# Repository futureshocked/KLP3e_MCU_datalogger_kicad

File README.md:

View this project on [CADLAB.io](https://cadlab.io/project/24569). 

# MCU datalogger, a Kicad project

This is the repository for the "MCU datalogger" project.

This is one of the projects from the course [KiCad Like a Pro, 3rd edition](https://techexplorations.com/so/kicad-like-a-pro-3rd-edition/).

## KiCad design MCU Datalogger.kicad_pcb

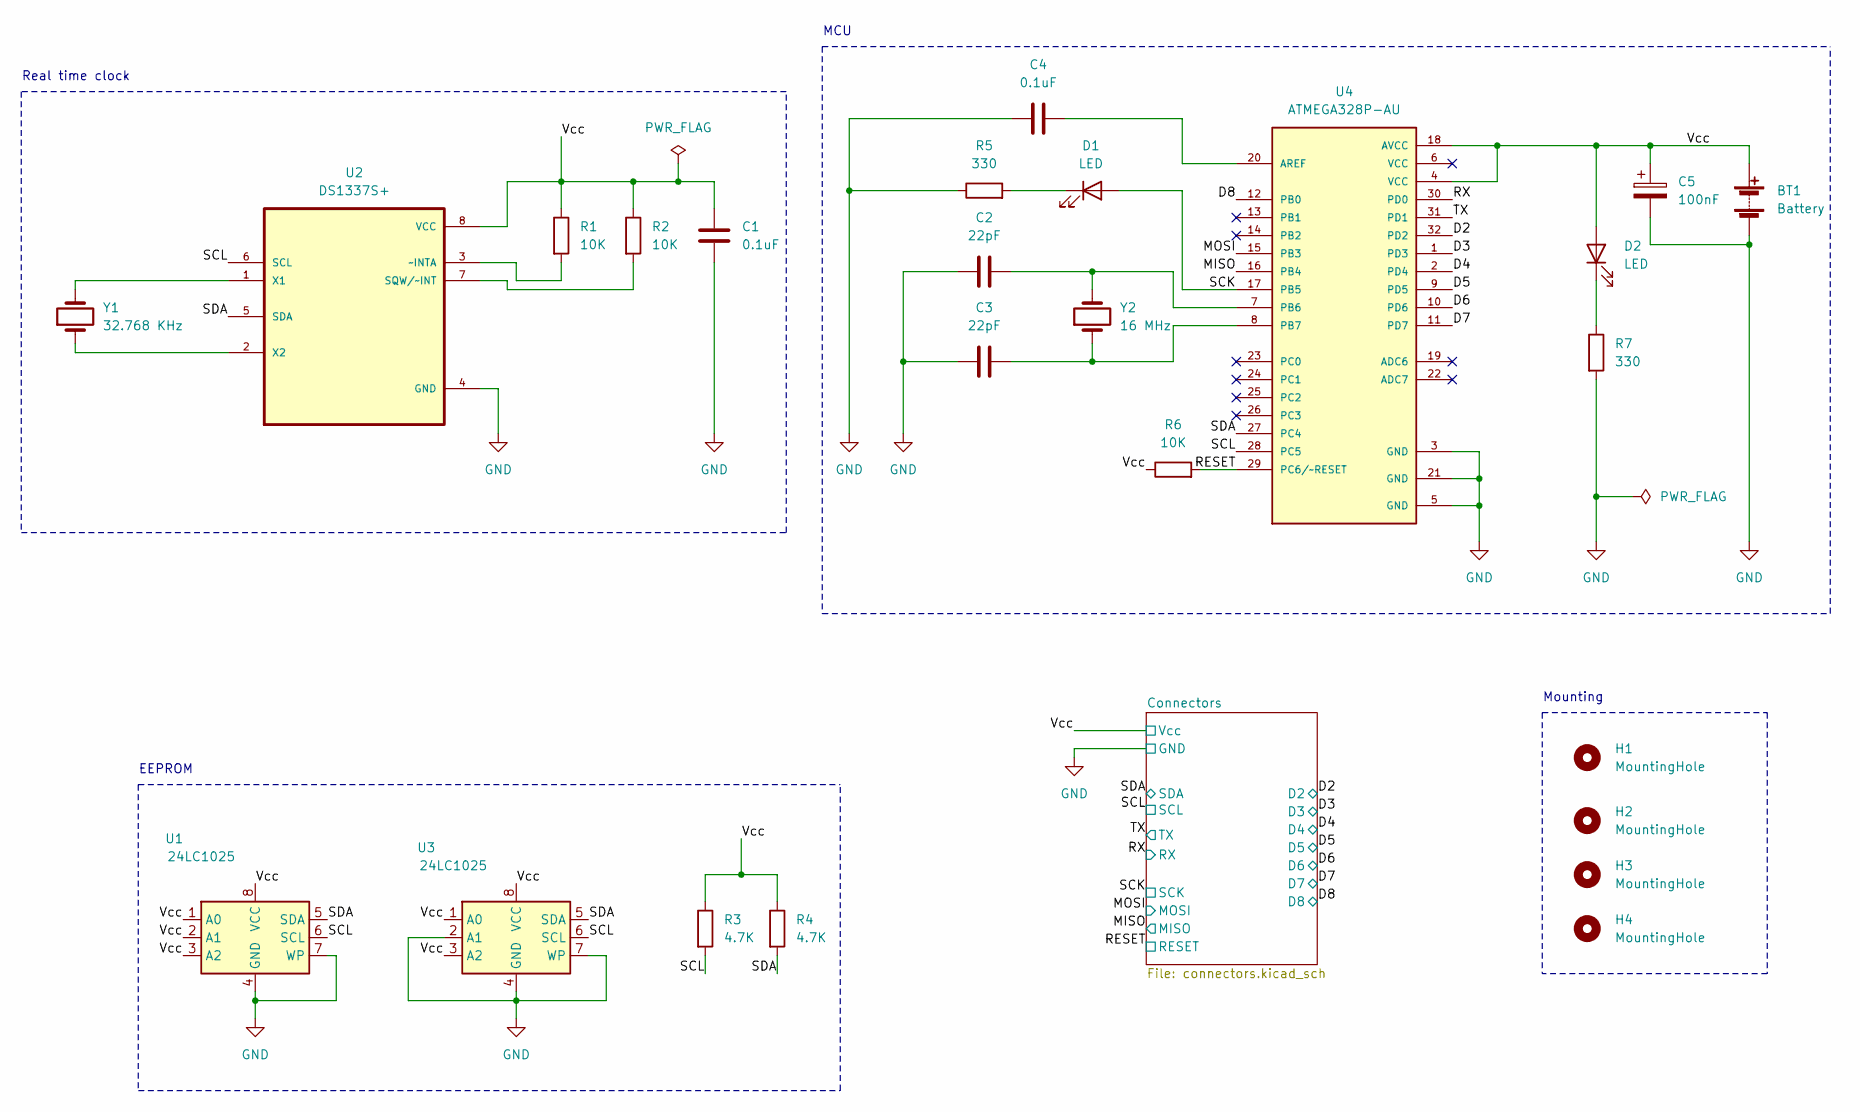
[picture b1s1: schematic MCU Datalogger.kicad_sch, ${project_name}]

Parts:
BT1: Battery; PinHeader_1x02_P2.54mm_Vertical
C1, C4: 0.1uF; C_0805_2012Metric
C2, C3: 22pF; C_0805_2012Metric
C5: 100nF; C_0805_2012Metric
D1, D2: LED; LED_0805_2012Metric
H1, H2, H3, H4: MountingHole; MountingHole_2.1mm
R1, R2, R6: 10K; R_0805_2012Metric
R3, R4: 4.7K; R_0805_2012Metric
R5, R7: 330; R_0805_2012Metric
U1, U3: 24LC1025; SOIC-8_5.23x5.23mm_P1.27mm
U2: DS1337S+; SOIC127P600X175-8N
U4: ATMEGA328P-AU; QFP80P900X900X120-32N
Y1: 32.768 KHz; Crystal_SMD_5032-2Pin_5.0x3.2mm_HandSoldering
Y2: 16 MHz; Crystal_SMD_5032-2Pin_5.0x3.2mm_HandSoldering

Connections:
/D2: U4.32 (PD2); also elsewhere on the board
/D3: U4.1 (PD3); also elsewhere on the board
/D4: U4.2 (PD4); also elsewhere on the board
/D5: U4.9 (PD5); also elsewhere on the board
/D6: U4.10 (PD6); also elsewhere on the board
/D7: U4.11 (PD7); also elsewhere on the board
/D8: U4.12 (PB0); also elsewhere on the board
/MISO: U4.16 (PB4); also elsewhere on the board
/MOSI: U4.15 (PB3); also elsewhere on the board
/RESET: R6.2, U4.29 (PC6/~RESET); also elsewhere on the board
/RX: U4.30 (PD0); also elsewhere on the board
/SCK: D1.2 (A), U4.17 (PB5); also elsewhere on the board
/SCL: R3.2, U1.6 (SCL), U2.6 (SCL), U3.6 (SCL), U4.28 (PC5); also elsewhere on the board
/SDA: R4.2, U1.5 (SDA), U2.5 (SDA), U3.5 (SDA), U4.27 (PC4); also elsewhere on the board
/TX: U4.31 (PD1); also elsewhere on the board
/Vcc: BT1.1 (+), C1.1, C5.1, D2.2 (A), R1.1, R2.1, R3.1, R4.1, R6.1, U1.1 (A0), U1.2 (A1), U1.3 (A2), U1.8 (VCC), U2.8 (VCC), U3.1 (A0), U3.3 (A2), U3.8 (VCC), U4.4 (VCC), U4.18 (AVCC); also elsewhere on the board
GND: BT1.2 (-), C1.2, C2.1, C3.1, C4.1, C5.2, R5.1, R7.2, U1.4 (GND), U1.7 (WP), U2.4 (GND), U3.2 (A1), U3.4 (GND), U3.7 (WP), U4.3 (GND), U4.5 (GND), U4.21 (GND); also elsewhere on the board
unnamed: C2.2, U4.7 (PB6), Y2.2
unnamed: C3.2, U4.8 (PB7), Y2.1
unnamed: C4.2, U4.20 (AREF)
unnamed: D1.1 (K), R5.2
unnamed: D2.1 (K), R7.1
unnamed: R1.2, U2.3 (~INTA)
unnamed: R2.2, U2.7 (SQW/~INT)
unnamed: U2.1 (X1), Y1.2
unnamed: U2.2 (X2), Y1.1

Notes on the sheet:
Mounting
EEPROM
MCU
Real time clock

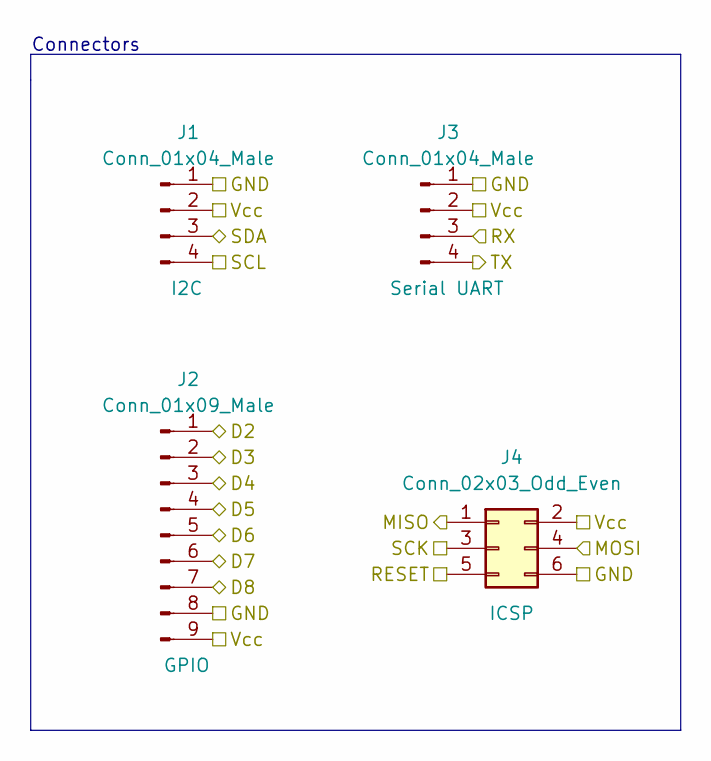
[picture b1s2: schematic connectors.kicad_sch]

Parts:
J1, J3: Conn_01x04_Male; PinHeader_1x04_P2.54mm_Vertical
J2: Conn_01x09_Male; PinHeader_1x09_P2.54mm_Vertical
J4: Conn_02x03_Odd_Even; PinHeader_2x03_P2.54mm_Vertical

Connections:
/D2: J2.1; also elsewhere on the board
/D3: J2.2; also elsewhere on the board
/D4: J2.3; also elsewhere on the board
/D5: J2.4; also elsewhere on the board
/D6: J2.5; also elsewhere on the board
/D7: J2.6; also elsewhere on the board
/D8: J2.7; also elsewhere on the board
/MISO: J4.1; also elsewhere on the board
/MOSI: J4.4; also elsewhere on the board
/RESET: J4.5; also elsewhere on the board
/RX: J3.3; also elsewhere on the board
/SCK: J4.3; also elsewhere on the board
/SCL: J1.4; also elsewhere on the board
/SDA: J1.3; also elsewhere on the board
/TX: J3.4; also elsewhere on the board
/Vcc: J1.2, J2.9, J3.2, J4.2; also elsewhere on the board
GND: J1.1, J2.8, J3.1, J4.6; also elsewhere on the board

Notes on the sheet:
Connectors

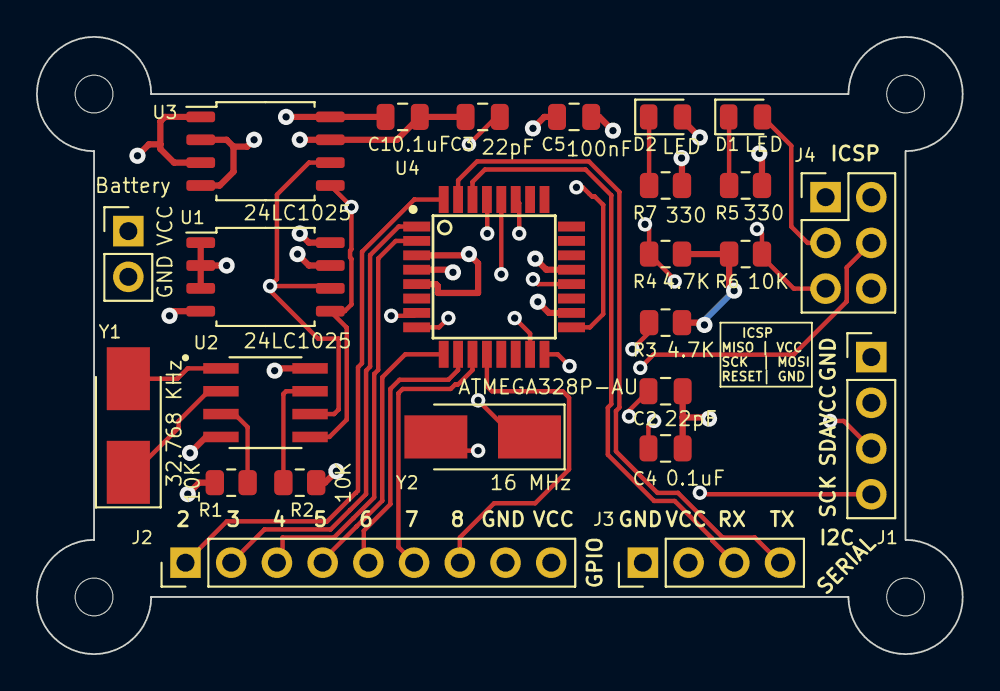
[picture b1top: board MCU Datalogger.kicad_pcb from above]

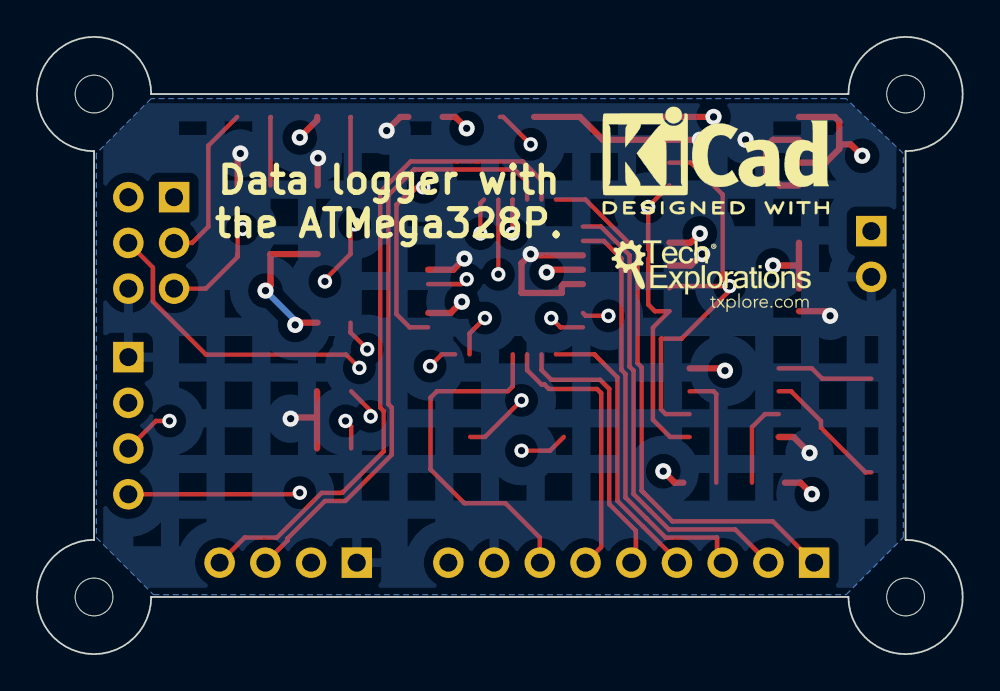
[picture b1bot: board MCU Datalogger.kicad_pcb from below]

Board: 4 copper layers, 51.4 x 34.3 mm, 31 parts (2 on the bottom side), 26 nets.

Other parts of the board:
G2: LOGO; TE_Logo_11.6x4
REF1: KiCad-Logo2_5mm_SilkScreen

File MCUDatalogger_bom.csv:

"Id";"Designator";"Package";"Quantity";"Designation";"Supplier and ref";
1;"H4,H1,H2,H3";"MountingHole_2.1mm";4;"MountingHole";;;
2;"R1,R6,R2";"R_0805_2012Metric";3;"10K";;;
3;"U3,U1";"SOIC-8_5.23x5.23mm_P1.27mm";2;"24LC1025";;;
4;"R4,R3";"R_0805_2012Metric";2;"4.7K";;;
5;"C1,C4";"C_0805_2012Metric";2;"0.1uF";;;
6;"J3,J1";"PinHeader_1x04_P2.54mm_Vertical";2;"Conn_01x04_Male";;;
7;"C2,C3";"C_0805_2012Metric";2;"22pF";;;
8;"D1,D2";"LED_0805_2012Metric";2;"LED";;;
9;"R7,R5";"R_0805_2012Metric";2;"330";;;
10;"J4";"PinHeader_2x03_P2.54mm_Vertical";1;"Conn_02x03_Odd_Even";;;
11;"Y2";"Crystal_SMD_5032-2Pin_5.0x3.2mm_HandSoldering";1;"16 MHz";;;
12;"BT1";"PinHeader_1x02_P2.54mm_Vertical";1;"Battery";;;
13;"C5";"C_0805_2012Metric";1;"100nF";;;
14;"U4";"QFP80P900X900X120-32N";1;"ATMEGA328P-AU";;;
15;"J2";"PinHeader_1x09_P2.54mm_Vertical";1;"Conn_01x09_Male";;;
16;"U2";"SOIC127P600X175-8N";1;"DS1337S+";;;
17;"Y1";"Crystal_SMD_5032-2Pin_5.0x3.2mm_HandSoldering";1;"32.768 KHz";;;
18;"G2";"TE_Logo_11.6x4";1;"LOGO";;;
19;"G***";"TE_Logo_10mm_negative_silkscreen";1;"LOGO";;;
20;"REF1";"KiCad-Logo2_5mm_SilkScreen";1;"KiCad-Logo2_5mm_SilkScreen";;;

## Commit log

2021-07-20 First commit of new project.
2021-07-20 Setup of EEschema for new project.
2021-07-20 Have added required symbols to the schematic sheets.
2021-07-20 Changed locations of symbols (arrange).
2021-07-20 Added component values.
2021-07-20 Completed symbol-footprint associations.
2021-07-20 Completed wiring of main sheet.
2021-07-20 Completed wiring in the second sheet.
2021-07-20 Allocated GND and Vcc nets to the Power net class.
2021-07-20 Completed comments.
2021-07-21 Fixing typos.
2021-07-21 Setup Pcbnew.
2021-07-21 Completed placement of footprints.
2021-07-21 Refined and completed outline.
2021-07-21 Routing sans GND Vcc complete.
2021-07-21 Completed routing.
2021-07-21 Refined routing complete.
2021-07-22 Fixed outstanding issues.
2021-07-22 Completed 2-layer PCB project.
2021-07-22 Completed 2-layer PCB.
2021-07-22 Added gerber directories to gitignore.
2021-07-22 Completed 4-layer pcb routing.
2021-07-22 Added board characteristics.
2021-07-22 Made small change to schematic.
2021-07-22 Added gitattributes file to preven PCB files from merge.
2021-07-22 Imported changes from schematic.
2021-07-23 Tidying up.
2021-07-23 Added dsn files in the ignore list.
2021-07-25 Edited gitignore file.
2021-07-25 Unrouted 2-layer board.
2021-07-25 Added automaticaly routed 2-layer board.
2021-07-26 Added auto 4-layer routing.
2021-07-26 Demonstrating custom track and via sizes.
2021-07-26 Made a small change.
2021-07-26 Replaced straigh track with jagged track.
2021-07-27 Changes due to various feature demos.
2021-07-27 Added custom graphics.
2021-07-27 Generated reports.
2021-07-28 Demonstrating origins and axes.
2021-07-28 Generated BOM.
2021-07-29 Added README.
2021-07-29 Backlink to CADLAB.io has been added.
2021-12-07 Fixed errata #106
    I2C clock should be named SCL and not connected to SPI click net SCK
